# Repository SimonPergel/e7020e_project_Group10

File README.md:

# e7020e_project
We shamelessly borrowed the footprint & symbol libraries used in the labs of E7020E

# TOTP with automatic password input

## Members

- Gabriel Axheim Gustafsson (gabaxh-2@student.ltu.se)
- Patrik Wall (walpat-1@student.ltu.se)
- Simon Pergel (isoepe-1@student.ltu.se)

## High level specification
Our TOTP fob is designed to be able to automatically input the password calculated by behaving like a keyboard when you click the button once and it's connected to the USB, holding the button down will instead make it behave like a usb memory thus allowing a user to insert a new secret onto the device. When the password has been sent the display will show a "Success" message letting the user know that it's safe to remove the device. When the device is only powered by battery the device will show the one time password on the display instead, holding down the button will instead show the secret stored on the device.
- Button
  - Click, USB powered: calculate & act as keyboard (enters password automatically)
  - Click, battery powered: calculate password and show it on the display
  - Hold, USB powered: allow insertion of secrets
  - Hold, battery powered: display secret
- Display
  - If button was clicked show password (battery)
  - If button was clicked send password (usb)
    - Show successful message when password was "sent"
  - If button was held & connected to USB
    - Restart USB connection & act as a USB memory
    - Allow a user to store new secret

NOTE: This is still not set in stone, currently talking about it and might change
### Hardware Features
- 1x Real time clock (32kHz crystal)
- 1x Button
- 1x USB connector
- 1x Display
- 1x Battery connector (5V)

### Software Features
- Allow setting & getting time
- Set shared secret
- Encrypt secret
- Deep sleep (1mA during idle)

### Additional features
- Battery powered while not connected to USB
- Allowing the TOTP to switch between different behaviour
  - Might need to terminate USB connection for this to work
  - Acting as a keyboard
  - Acting as a USB memory auto running a CLI?
- *LED displaying remaining battery

Features starting with * might be included depending on difficulty and time required to complete said feature

## Grading
- Gabriel
  - Expected contributions towards grade 4 or 5.

- Simon
  - Expected contributions towards grade 4 or 5.
 
- Patrik
   - Expected contributions towards grade 4 or 5.

## Summary of workflow and member contribution

Regarding our goal, it turned out to be very hard to achive all features due to faults in the final PCB manufactured board (as brought up on presentation meeting), which led to delays and alot of time-pressure towards the end. But overall, we are very happy that we manage to do in the time we had. Working button, working keyboard feature, working Secret-key storeage on the flash memory on the pcb and also a correct working OTP-code generator. 

- Contribution
  - When it comes to hardware, we decided to do everything as a group together, mostly because all of us wanted to learn soldering and the whole process.
  - When it comes to the software, we reused alot of code from the excercises. But we assignt our selfs to be responsible for diffrent task inside the software. Gabriel was responsable for getting the pcb to work as a keyboard and get the button up and running. Patrik took upon himself to implement the secret key store/retrieval-feature and helping Simon with the display. Simon was responsible for how the otp-code was generated and at the end tried with Patrik to get the display to work. Ofcourse there had to be alot of pair/group programing because our parts had to work together and in the "same direction". So alot of times there where open discussion where ideas was floating in the air and changes was made.

- NOTE: our code is not very well structred(due to time press), but important to know is that our working software is placed inside a file named "examples/main.rs". There are also some things added in the cargo files and in the command-parser file, but the main software is in main.rs. There may also be code that is not yet finished (display), if that is a problem let us know.

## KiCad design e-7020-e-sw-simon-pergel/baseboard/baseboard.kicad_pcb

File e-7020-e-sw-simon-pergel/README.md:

# RTIC on the nRF52840DK board

## Resources

- [nrf52840 Product Specification](https://docs.nordicsemi.com/bundle/ps_nrf52840/page/keyfeatures_html5.html), you may also download the Product Specification (v1.11) as a pdf.

- [Table of processor instructions](https://developer.arm.com/documentation/100166/0001/Programmers-Model/Instruction-set-summary/Table-of-processor-instructions?lang=en), for the Cortex M4 architecture. You may also download the whole Cortex-M4 Technical reference manual.

- [ARM and Thumb-2 Instruction Set Quick Reference Card](https://developer.arm.com/documentation/qrc0001/m), pdf only.

---

## Rust

We assume Rust to be installed using [rustup](https://www.rust-lang.org/tools/install).

Additionally you need to install the `thumbv7em-none-eabihf` target. You may also want to inspect generated binaries using `llvm-tools`.

```shell
rustup target add thumbv7em-none-eabihf
rustup component add llvm-tools
```

---

## Cargo sub-commands

The `cargo` tool is used to manage your applications. You may find the following extensions useful.

- `cargo-edit`, allows you to manage dependencies from the command line.

- `cargo-update`, allows you to update all cargo installed utilities by running:

  `cargo install-update -a`

- `cargo-tree`, allows you to see all dependencies brought in by your application.

```shell
cargo install cargo-edit cargo-update cargo-tree
```

## Rust Embedded

We assume the following tools are in place:

- [cargo-binutils](https://github.com/rust-embedded/cargo-binutils)

- [cargo-bloat](https://github.com/RazrFalcon/cargo-bloat)

- [nrf-unlock](https://github.com/perlindgren/nrf-unlock)

- [probe-rs](https://github.com/probe-rs/probe-rs)

```shell
cargo install cargo-binutils cargo-bloat
cargo install probe-rs --locked --features=cli
cargo install --git https://github.com/perlindgren/nrf-unlock
```

---

## Nordic utilities

Tools for working with the Nordic range of MCUs. Under arch you can install them through `aur`:

```shell
yay nrf5x-command-line-tools
```

To unlock the 52840DK (allowing you to program it over SWD), you can either use the `nrf-unlock` (see above) or the `nrfjprog` tool.

run:

```shell
nrfjprog --recover
```

This operation might take some time (it erases the complete flash memory and flash protection bits).

Notice, the nRF 52840DK comes with the flash protected, so you must run `nrfjprog --recover` to unlock the device.

---

## For low level `gdb` based debugging (optional)

Linux tooling:

- `openocd`
- `arm-none-eabi-gdb`, or`gdb-multiarch` (if running under ubuntu/debian)

Install these tools using your package manager.

---

## Editor

You may use any editor of choice. We recommend `vscode`, the `rust-analyzer` and `probe-rs debugger` plugins. There are many other great plugins for improved git integration, `.md` linting and preview etc.

In the `.vscode` folder of this project, you find a number of configuration files (`launch.json` for target debugging, `tasks.json` for building, etc.), that facilitates embedded Rust development.

For installing the `probe-rs debugger` follow the instructions [here](https://probe.rs/docs/tools/vscode/).

The [vscode](https://marketplace.visualstudio.com/items?itemName=probe-rs.probe-rs-debugger) plugin is now available also from the marketplace (last checked 2024-02-12).

---

All tools are available under both Linux, OSX, and Windows.

## Windows

To use `probe-rs` under Windows you need to install the WinUSB driver. Notice this might class with the `JLink` usb driver installed by the `nRF-Command-Line-Tools`, so I would recommend using `probe-rs` based tooling instead (see above).

- [zadig](https://zadig.akeo.ie/)
- [nRF-Command-Line-Tools](https://www.nordicsemi.com/Products/Development-tools/nRF-Command-Line-Tools/Download?lang=en#infotabs)

## OSX

Should work as described for (arch) Linux. The package manager `brew` or `macports` are your friends. OSX and Linux shares the same POSIX (Unix) heritage, for the OSX case it is based on a classic BSD kernel implementation. `brew`relies to large degree on the OSX system libraries, while `macports`installs dependencies from source (which might take longer time, but reduces the risk of library incompatibilities).

If you run into weird Rust compilation/tooling problems, check you packaga manager to make sure it has not installed any Rust related stuff (rustc, cargo, rustup etc.). Duplicatie toolchains may lead to very strange problems/errors.

---

## Other Useful Resources

- General Embedded
  - [Introduction to SPI](https://www.analog.com/en/analog-dialogue/articles/introduction-to-spi-interface.html#), a short introduction to the SPI interface.

---

## Setup

This crate is contains a ready made configuration for compiling, running/tracing Rust RTIC on the `nRF52840 DK`.

- `Cargo.toml` specifies all dependencies.

- `.cargo/config.toml` specifies further build options. By default `cargo run` will use `probe-run` as specified:

  ```toml
  runner = "probe-rs --chip nRF52840_xxAA"
  # runner = "probe-rs --chip nRF52833_xxAA --no-default-features --features 52833"

  ```

---

## Examples

### Terminal trace using RTT on the nrf52840 DK

Select the runner in `.cargo/config.toml`:

```shell
runner = "probe-rs --chip nRF52840_xxAA"
```

Run your application from terminal:

```shell
cargo run --example rtic_hello
```

(Press Ctrl-C to exit.)

Tracing of panics is supported by the `panic_rtt` crate.

### Terminal trace using RTT using the nrf52840 DK to program an nrf528433 target

Connect the SWD cable to the target. Target needs to be separately powered at 3.0-3.3v unless a level shifter is used in between the DK and the target MCU.

Select the runner in `.cargo/config.toml`:

```shell
runner = "probe-rs --chip nRF52833_xxAA --no-default-features --features 52833"
```

Run your application from terminal:

```shell
> cargo run --example rtic_hello_52833
```

---

### VSCODE based debug and trace examples for the nrf52840 DK

Some simple bare metal examples for you to try out before starting to run your own code: (Here we assume the tools mentioned above have been successfully installed into their default locations. If you installed manually, you may need to tweak paths accordingly, ask in the `software` channel on Discord if you run into some trouble.)

Enable debug view (Ctrl-D), select either `probe-rs Debug` or `probe-rs Release` profile. Press F5 to launch and debug the program in the currently active `vscode` window.

- `rtic_hello.rs`, this example prints the output in the `TERMINAL` pane.
- `rtic_panic.rs`, this example shows how to trace panic messages (in this case over RTT.

- `rtic_crash.rs`, this example shows how a HardFault can be caught by a custom handler.

- `rtic_blinky.rs`, this example shows how you can setup a `SysTick` timer to get a periodically blinking LED without accumulated drift.

- `rtic_usb_serial.rs`, this example showcase a Virtual Com Port (VCP) over USB ACM/CDC using the target USB port of the `nRF52840 DK`

  - Connect a micro USB cable between the host and the target MCU.
  - On the host run a serial terminal (e.g. `cutecom`) and connect to `/dev/ttyACMx` with a setting of 115200 N1.
  - The target application will echo back text sent in upper case.

- `rtic_usb_mouse.rs`, this example emulates a mouse over USB-HID.

  - Connect a micro USB cable between the host and the target MCU.
  - The target will wiggle your mouse pointer.

- `rtic_usb_serial_interrupt.rs`, this example showcase how to make a USB device interrupt driven. The trick is that you need to give the `usb-bus` and `serial` device driver a `'static` lifetime (i.e., these need to live on forever). Normally the lifetime of a variable (resource) is only its local scope. What we do here is to declare the `usb_bus` and `serial` driver as `local` resources to init (those will have a `'static` lifetime). We use the `Option` type to be able to give them a `None` value initially (in Rust all variables need to hold a valid value, thus we need to initialize them). Once the `usb_dev` and `serial` have been constructed we can `replace` the `None` values correspondingly. One can refer to the _inner_ `Some` of the `Option` by `as_ref().unwrap()`. Using this pattern all user code can be written in _safe_ Rust.

- `rtic_paw3395`, minimal viable example for setup and use of the PixArt paw3395 sensor.

- `rtic_cpi_paw3395`, minimal viable example for reading and setting cpi.

Notice, for now we disabled the setup sequence as it seems to fail calibration and make communication instable (reason unknown). Default (boot settings) seems to render satisfiable results.

### VSCODE based debug and trace examples for the nrf52840 DK to program an nrf528433 target

For connecting the DK and general vscode debugging, see above.

Select either `52833 probe-rs Debug` or `52833 probe-rs Release` profile.

- `rtic_hello_52833.rs`, this example prints the output in the `TERMINAL` pane.
- `rtic_usb_mouse_52833`, this example emulates a mouse over USB-HID.

Under the hood, the Rust feature system is used: by default the `52840` is used to select the `nrf52840` target. Building for the `nrf52833` is done by `--no-default-features --features 52833`.

### Cargo Embed

For the `nrf52840 DK` run:

```shell
cargo embed --example rtic_hello
```

Alternatively to manually run:

```shell
cargo embed --example rtic_hello_52833 --no-default-features --features 52833
```

---

### Debugging using GDB (optional)

Select the runner in `.cargo/config.toml` according to your `gdb` install, e.g.:

```shell
runner = "arm-none-eabi-gdb -q -x openocd.gdb"
```

Start `openocd` in a separate terminal:

```shell
> openocd -f openocd.cfg
```

Run the application: e.g.

```shell
> cargo run <application>
```

The `openocd.gdb` script is used to setup the behavior of the debug session, you may change it to your liking. (The default script puts breakpoints at `DefaultHandler`, `HardFault` and `main`, edit it for your needs.)

### Gdb the GNU debugger (optional)

Gdb offers a lot of functionality, you may even write scripts in python to automate debugging. For a summary of commands see e.g., [gdb-refcard](http://fac-staff.seattleu.edu/elarson/web/Linux/gdb-refcard.pdf).

Many of the commands can be executed from the `DEBUG CONSOLE` in `vscode`.

---

## Concluding remarks on debug and trace

Chose the approach and tools dependent on your application needs. If plain tracing is sufficient chose `probe run` or for more flexibility `cargo embed`. If you need to interactively debug your application, use the `probe-rs` vscode integration.

You may also look at [defmt](https://crates.io/crates/defmt), it supports deferred formatting to reduce the run-time overhead (on the target).

---

## Logic Analyzer

The `Hobby Components` [HCTEST0006](https://hobbycomponents.com/testing/243-hobby-components-usb-8ch-24mhz-8-channel-logic-analyser) is a low-cost entry level 8 channel logic analyzer.

It is supported by the [sigrok](https://sigrok.org/wiki/Main_Page) open source signal analysis software suit. The [PulseView](https://sigrok.org/wiki/PulseView) tool is an all in one frontend for digital oscilloscopes and logic analyzers.

Install the `pulseview` tool and the `sigrok-firmware-fx2lafw`. Under arch run:

```shell
yay pulseview sigrok-firmware-fx2lafw
```

For setting up `udev` rules follow the instructions [here](https://gist.github.com/thefekete/7995329c8370cb511a080ee441212b41). This allows you to run the `pulseview` tool as user (else you need `sudo` to get access to the USB device).

### Setup Logic Analyzer

Check that your analyzer turns up as a USB device:

```shell
lsusb
...
Bus 003 Device 009: ID 1d50:608c OpenMoko, Inc. Fx2lafw
```

Now you can start the `pulseview` tool.

- Connect To Device
  - Step 1 select `fx2lafw (...)`,
  - Step 2 make sure that `USB` is selected
  - Step 3 Press : `Scan for devices`
  - Step 4 Select the `sigrok FX2 LO (8ch) ...`
  - Step 5 Press OK.

Now you should be able select sample rate (up to 24MHz) and number of samples and run a capture.

### Trouble shooting

If you don't see the `fx2lafw` alternative among selectable device drivers, then you have a problem with your `sigrok-firmware-fx2lafw` install. If you can select it but the `Scan for devices` is not available or fails, then you have a problem with the permissions (or operating system usb driver). This is highly system dependent, for linux based systems permissions are typically managed/set using `udev` rules as described above.

## Logic Analyzer Nordic PPK2

The Nordic Power Profiler Kit II is a desgined to measure Power consumption of embedded devices. It also comes with a primitive Logic analyzer, that can to track up to 8 channels. To get started install the nRF Connect for Desktop tool. It is available for the Major Platforms (Linux, macOS and Windows) here: https://www.nordicsemi.com/Products/Development-tools/nRF-Connect-for-Desktop/Download. The tool is a "Launchpad" for different subtools. We are interested in the Power Profiler. Install and then launch it. 
Here are some steps you can test your PPK2 as Logic Analyzer:
Flash the test_ppk example to your devboard: `cargo run --example test_ppk`
This application is almost the same as rtic_bare4 with the exception that P1.13 is turned off and on with P0.13 (LED1). P1.13 is particularly pratical because it is exposed via a male Pin on the Devboard (Pretty central in a 2x3 Pin Header). Connect that Pin to Channel 0 of your PPK2. Now the logic analyzer needs a source of logical 0 (0V / GND) and a source of logical 1 (3.3V / VDD nRF). Attach the GND cable of the PPK2 to the extarnal Supply (-) Pin. It is located on the left Hand side of the DevKit below the USB-Connector. Finally attach the VCC cable of the PPK2 to the VDD nRF PIN. It is the leftmost PIN in the large horizontal male Pin-Header.

After all cables are set up, make sure that the devboard is running (you can check whether LED1 is blinking nicely). Connect your PPK2, make sure the switch is turned on and that you use the correct USB-Plug (USB DATA/POWER). In the power Profiler Application you should see the PPK2 now, select it. Enable at least digital Channel 0 and click start. If everything works correctly you should see a nice squarewave on the digital signal graph. The digital-channels graph is very small and in between the Log-window and the large power-consumption graph. Unfortunately the PowerProfiler Software is not too sophisticated but you can make your own measurements/calculations by hovering with the mouse and reading the timestamps.

---

## Exercises

Bare metal programming:

- `examples/rtic_bare1.rs`, in this exercise you learn about debugging, inspecting the generated assembly code, about checked vs. unchecked (wrapping) arithmetics. Provides essential skills and understanding of low-level (bare metal) programming.
- `examples/rtic_bare2.rs`, in this exercise you learn how to measure execution time using raw timer access.
- `examples/rtic_bare3.rs`, here you learn more about RTIC timing semantics and timing abstractions.
- `examples/rtic_bare4.rs`, in this exercise you will encounter a simple bare metal peripheral access API. The API is very unsafe and easy to misuse.
- `examples/rtic_bare5.rs`, here you will write your own peripheral access API. This API is much safer as you get control over bit-fields in a well defined way, thus less error prone.

- `examples/rtic_bare6.rs`, here you will write your own low-level driver and learn how to use a logic analyzer.

- `examples/rtic_bare7.rs`, here you will learn to use Monotonic timers and implement a timed protocol.

- `examples/rtic_bare8.rs`, here you will learn about serial communication. You will also learn how to work with external crates and how to write test.

- `examples/rtic_bare9.rs`, here you will learn more about `rtt` tracing, setting up a trace channel per RTIC priority level.

- `examples/rtic_bare10.rs`, here you will learn how to setup an ACM/CDC Virtual Com Port (VCP) over USB.

---

## Troubleshooting

---

### Fail to connect or program (flash) your target

- Make sure you have installed all the tools.

- Check that your `nRF52840 DK` is found by the host. You should see something like:

  ```shell
  > lsusb
  ...
  Bus 003 Device 009: ID 1366:1051 SEGGER J-Link
  ...
  ```

  - If not check your micro USB cable. Notice, you need a USB data cable (not a USB charging cable).

  - If the problem is still remains, there might be a USB issue with the host (or VM if you run Linux under a VM that is).

- If the device found by host:

  - If running in vscode reports an error like this:

    ```shell
    Caused by:
    0: An ARM specific error occurred.
    1: An operation could not be performed because it lacked the permission to do so: erase_all
    ```

    Then run the following command in the terminal:

    ```shell
    nrf-unlock
    ```

    or,

    ```shell
    nrfjprog --recover
    ```

    Or try using `cargo embed`.

  - In other cases, it might be your `nRF52840 DK`, try swapping cables and kits with other students.

- Don't hesitate to ask on the course Discord.

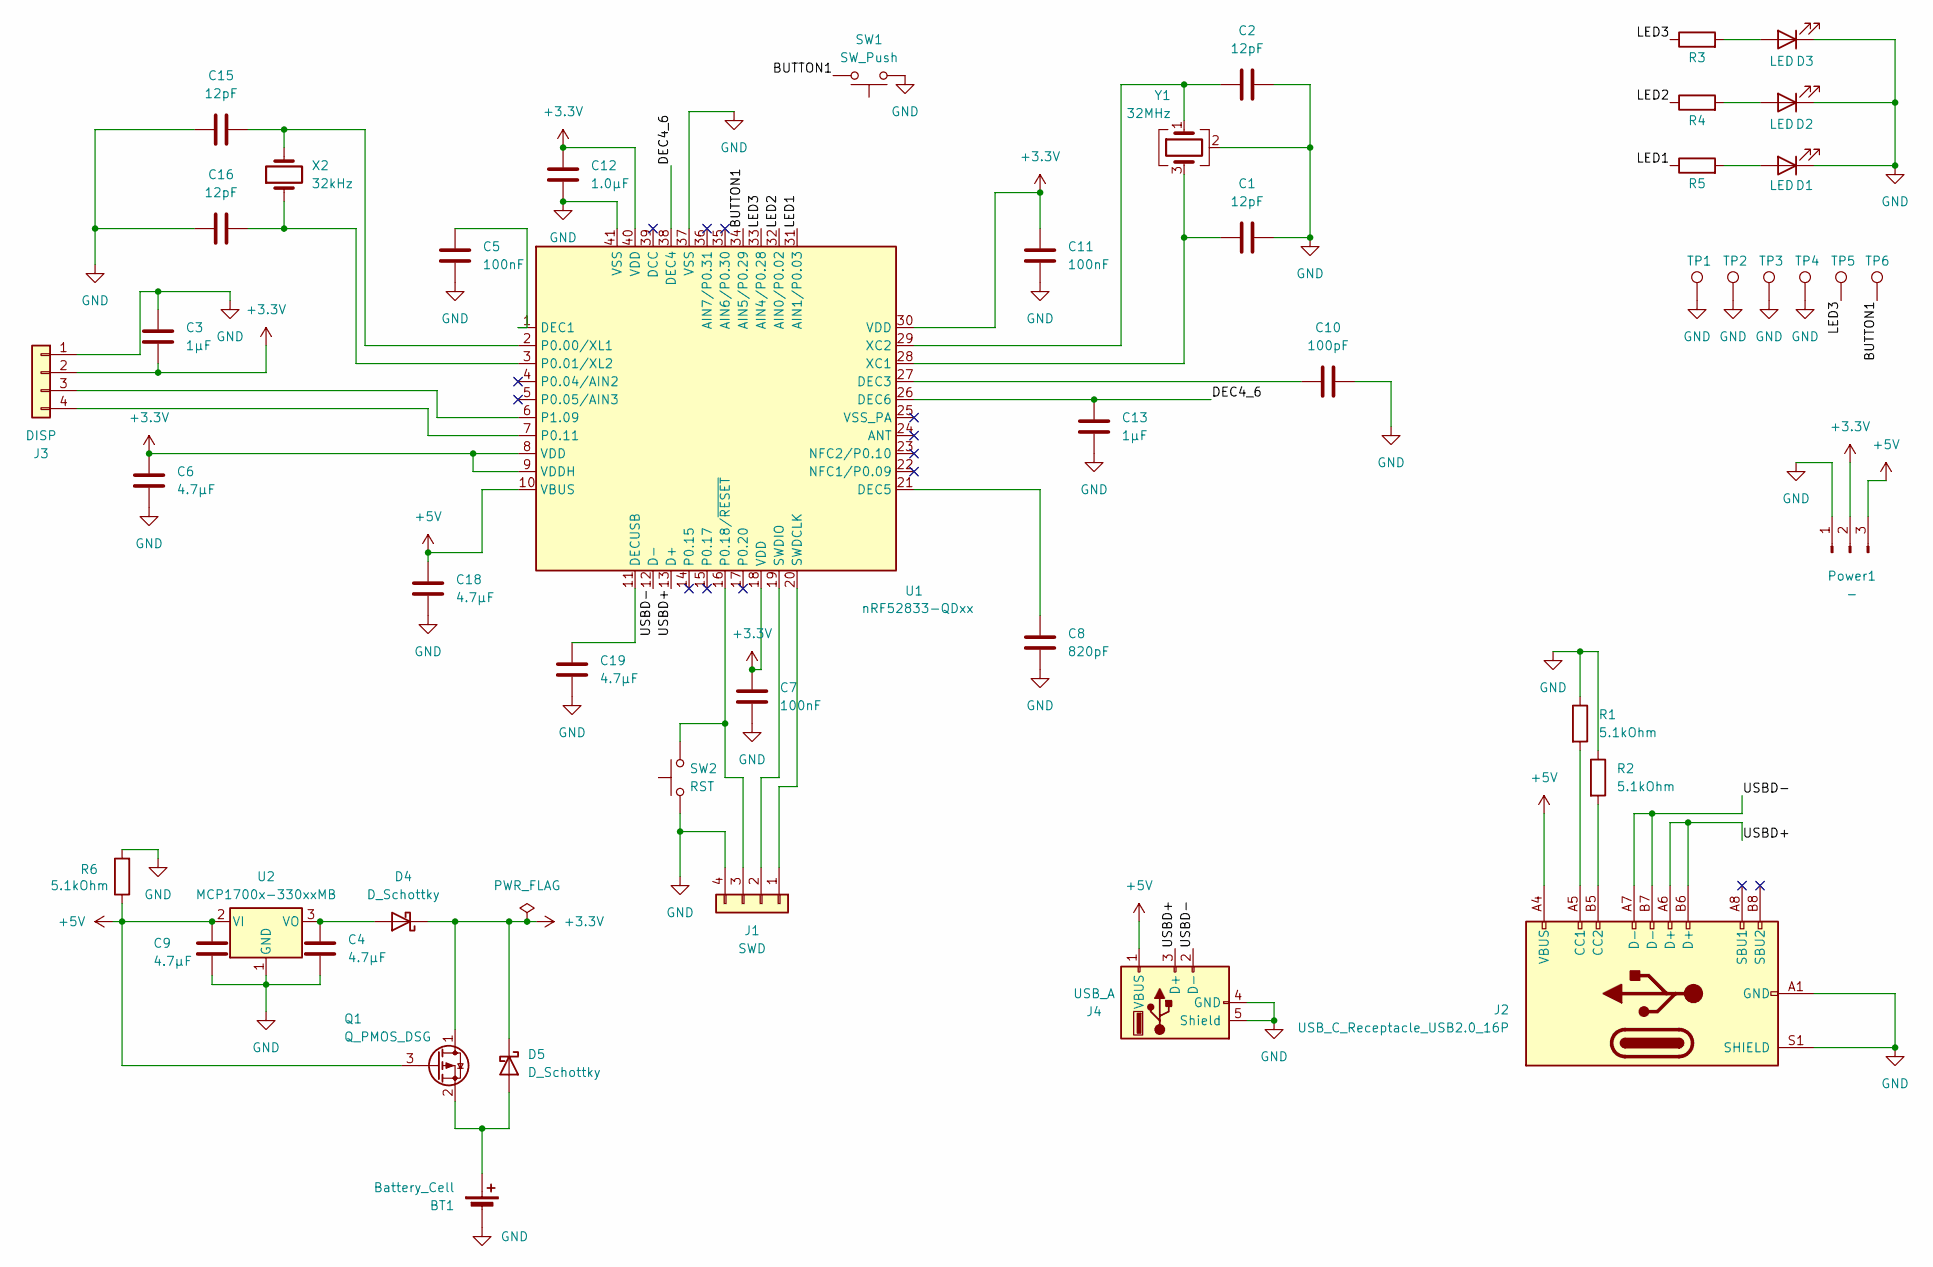
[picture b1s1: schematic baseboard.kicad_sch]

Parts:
BT1: Battery_Cell; BatteryHolder_Keystone_3002_1x2032
C1, C2, C15, C16: 12pF; C_0603_1608Metric
C3, C13: 1µF; C_0603_1608Metric
C4, C6, C9, C18, C19: 4.7µF; C_0603_1608Metric
C5, C7, C11: 100nF; C_0603_1608Metric
C8: 820pF; C_0603_1608Metric
C10: 100pF; C_0603_1608Metric
C12: 1.0µF; C_0603_1608Metric
D1, D2, D3: LED; LED_0805_2012Metric
D4, D5: D_Schottky; D_SOD-123
J1: SWD; PinHeader_1x04_P2.54mm_Vertical
J2: USB_C_Receptacle_USB2.0_16P; USB_C_Receptacle_GCT_USB4105-xx-A_16P_TopMnt_Horizontal
J3: DISP; PinHeader_1x04_P2.54mm_Vertical
J4: USB_A; USB_A_Molex_48037-2200_Horizontal
Power1: -; PinHeader_1x03_P2.54mm_Vertical
Q1: Q_PMOS_DSG; SOT-23
R1, R2, R6: 5.1kOhm; R_0603_1608Metric
R3, R4, R5: 330Ohm; R_0603_1608Metric
SW1: SW_Push; SW_PUSH_6mm
SW2: RST; SW_PUSH_6mm
TP1, TP2, TP3, TP4, TP5, TP6: TestPoint_THTPad_1.5x1.5mm_Drill0.8mm
U1: nRF52833-QDxx; QFN-40-1EP_5x5mm_P0.4mm_EP3.6x3.6mm
U2: MCP1700x-330xxMB; SOT-89-3
X2: 32kHz; Crystal_AT310_D3.0mm_L10.0mm_Horizontal
Y1: 32MHz; Crystal_SMD_3225-4Pin_3.2x2.5mm_HandSoldering

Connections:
+3.3V: C3.2, C6.1, C7.1, C11.1, C12.1, D4.1 (K), D5.1 (K), J3.2, Power1.2, Q1.1 (D), U1.8 (VDD), U1.9 (VDDH), U1.18 (VDD), U1.30 (VDD), U1.40 (VDD)
/BUTTON1: SW1.2, TP6.1, U1.34 (AIN5/P0.29)
/DEC4_6: C13.2, U1.26 (DEC6), U1.38 (DEC4)
/LED1: R5.1, U1.31 (AIN1/P0.03)
/LED2: R4.1, U1.32 (AIN0/P0.02)
/LED3: R3.1, TP5.1, U1.33 (AIN4/P0.28)
/USBD+: J2.A6 (D+), J2.B6 (D+), J4.3 (D+), U1.13 (D+)
/USBD-: J2.A7 (D-), J2.B7 (D-), J4.2 (D-), U1.12 (D-)
unnamed: BT1.1 (+), D5.2 (A), Q1.2 (S)
unnamed: D1.2 (A), R5.2
unnamed: D2.2 (A), R4.2
unnamed: D3.2 (A), R3.2
unnamed: C4.1, D4.2 (A), U2.3 (VO)
unnamed: J1.1, U1.20 (SWDCLK)
unnamed: J1.2, U1.19 (SWDIO)
unnamed: J1.3, SW2.2, U1.16 (P0.18/~RESET)
unnamed: J2.A5 (CC1), R1.2
unnamed: J2.B5 (CC2), R2.2
unnamed: J3.3, U1.6 (P1.09)
unnamed: J3.4, U1.7 (P0.11)
unnamed: C5.1, U1.1 (DEC1)
unnamed: C10.1, U1.27 (DEC3)
unnamed: C8.1, U1.21 (DEC5)
unnamed: C19.1, U1.11 (DECUSB)
unnamed: C15.2, U1.2 (P0.00/XL1), X2.2
unnamed: C16.2, U1.3 (P0.01/XL2), X2.1
unnamed: C1.1, U1.28 (XC1), Y1.3
unnamed: C2.1, U1.29 (XC2), Y1.1

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
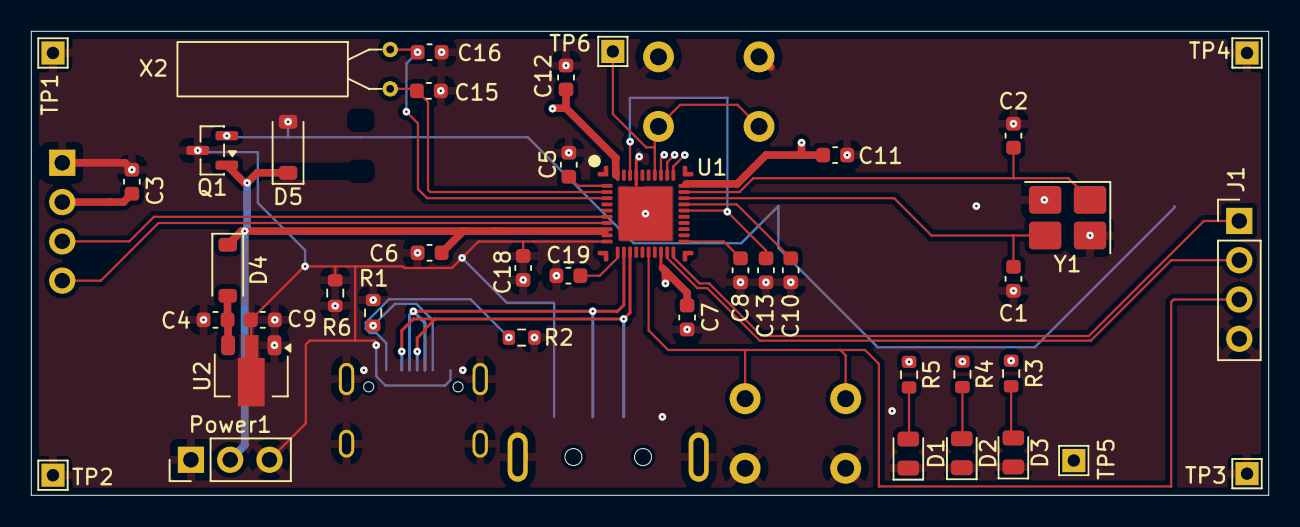
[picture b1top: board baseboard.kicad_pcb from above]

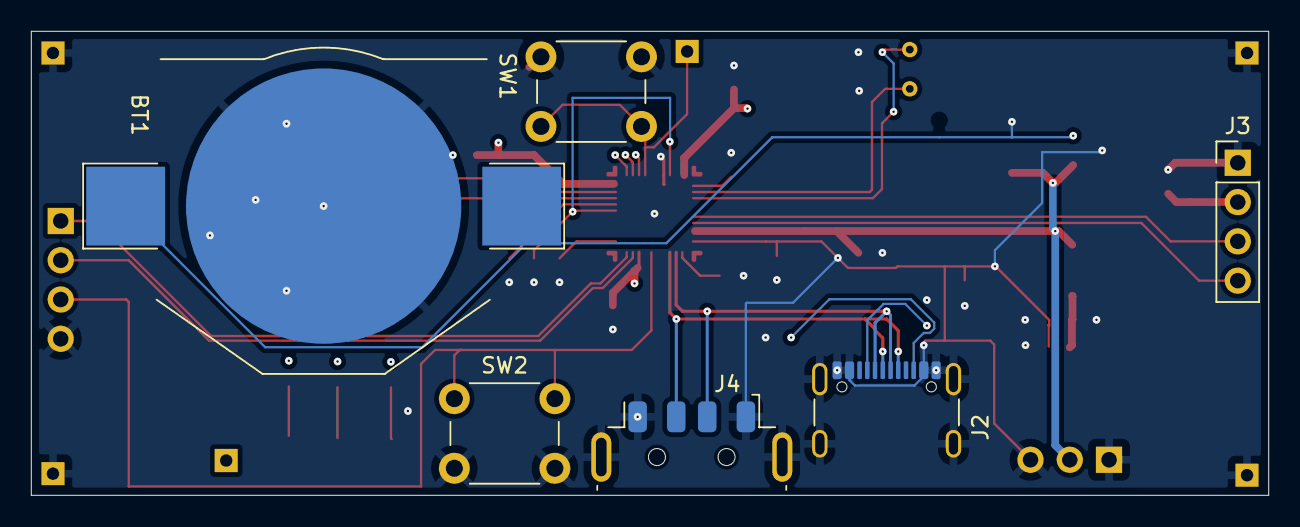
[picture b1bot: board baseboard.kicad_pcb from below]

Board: 4 copper layers, 80.0 x 30.0 mm, 47 parts (6 on the bottom side), 29 nets.

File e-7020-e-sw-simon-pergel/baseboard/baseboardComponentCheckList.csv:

Id;Designator;Footprint;Quantity;Designation;Supplier and ref;
1;R6,R2,R1;R_0603_1608Metric;3;5.1kOhm;;check
2;TP4,TP1,TP2,TP6,TP3,TP5;TestPoint_THTPad_1.5x1.5mm_Drill0.8mm;6;~;;check
3;J1;PinHeader_1x04_P2.54mm_Vertical;1;SWD;;check
4;C11,C5,C7;C_0603_1608Metric;3;100nF;;check
5;D1,D2,D3;LED_0805_2012Metric;3;LED;;check
6;C16,C15,C1,C2;C_0603_1608Metric;4;12pF;;check
7;C18,C4,C6,C19,C9;C_0603_1608Metric;5;4.7µF;;check
8;U2;SOT-89-3;1;MCP1700x-330xxMB;;check
9;Power1;PinHeader_1x03_P2.54mm_Vertical;1;-;;check
10;R5,R4,R3;R_0603_1608Metric;3;330Ohm;;check
11;C3,C13;C_0603_1608Metric;2;1µF;;saknad
12;D5,D4;D_SOD-123;2;D_Schottky;;check
13;X2;Crystal_AT310_D3.0mm_L10.0mm_Horizontal;1;32kHz;;check
14;C8;C_0603_1608Metric;1;820pF;;check
15;C10;C_0603_1608Metric;1;100pF;;check
16;Y1;Crystal_SMD_3225-4Pin_3.2x2.5mm_HandSoldering;1;32MHz;;check
17;C12;C_0603_1608Metric;1;1.0µF;;saknad
18;U1;QFN-40-1EP_5x5mm_P0.4mm_EP3.6x3.6mm;1;nRF52833-QDxx;;check
19;Q1;SOT-23;1;Q_PMOS_DSG;;check
20;SW1;SW_PUSH_6mm;1;SW_Push;;check
21;BT1;BatteryHolder_Keystone_3002_1x2032;1;Battery_Cell;;check
22;J4;USB_A_Molex_48037-2200_Horizontal;1;USB_A;;check
23;SW2;SW_PUSH_6mm;1;RST;;check
24;J2;USB_C_Receptacle_GCT_USB4105-xx-A_16P_TopMnt_Horizontal;1;USB_C_Receptacle_USB2.0_16P;;check
25;J3;PinHeader_1x04_P2.54mm_Vertical;1;DISP;;check

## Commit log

2026-01-30 Revise README with project details and features
    Updated README to provide detailed project specifications and features.
2026-01-30 Added example schematic & pcb, work in progress
2026-02-03 Finished schematic & pcb design with extra components
2026-02-05 Fixed PCB and added an extra USB-A connector
2026-02-05 Fixed pcb & schematic
2026-02-05 Fixed P-MOSFET and Schottky diode connected wrong on battery
2026-03-10 added the main software file
2026-03-10 commited my sw lab files for easy setup
2026-03-10 started with the generated opt functions
2026-03-11 added a new main file, added a shell structure
2026-03-11 cleaned up
2026-03-11 adding simple blink feature
2026-03-12 blinking feature
2026-03-13 Secret storage in flash WIP
2026-03-16 Code to write to the computer
2026-03-17 totp and time handeling
2026-03-18 Merged secret handler and totp calc
2026-03-18 Moved mod app } bracket
2026-03-18 totp func. in progress
2026-03-18 base32 impl.
2026-03-18 Decoded secret w/ base32ct before saving to flash
2026-03-18 Working secret storage & totp generation
2026-03-19 save opt code in shared var
2026-03-19 changed the shared code var to 6 indexes
2026-03-19 Added some fixes and comments
2026-03-19 Fixed some errors
2026-03-19 Working code?
2026-03-19 Should work
2026-03-19 Some changes
2026-03-19 Working code for everything
2026-03-20 Working code ready for Demo
2026-03-20 Update README.md
    Final workflow update
2026-03-20 repo cleanup
2026-03-20 Slight changes to README
2026-03-20 Fixed contribution title to match rest of README
